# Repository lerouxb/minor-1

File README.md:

# minor-1

Credit card sized capacitive touch toy piano.

Just the absolute minimum:

* QT60140 16 key touch sensor
* ATtiny1614 microcontroller
* Piezo transducer
* MCP6001R op-amp as buffer for the piezo
* CR2032 coin cell battery
* SPDT power switch
* 13 keys, octave +/- and change sound touch buttons
* Currently unpopulated footprint for NOR flash
* P-channel MOSFET for completely cutting power

This uses the attiny's 8-bit DAC at 25khz to play notes. The microcontroller can shut down power to the op-amp/piezo and the flash chip when not in use. It also sleeps until a touch button is pressed or until there's activity on the serial port.

There's a simple browser page to log the button presses, read status and read/write the setups. Useful for configurating the touch controller. Could be useful in future for programming the NOR flash or configuring the sounds.

Still very much a work in progress, but it can already play tunes.

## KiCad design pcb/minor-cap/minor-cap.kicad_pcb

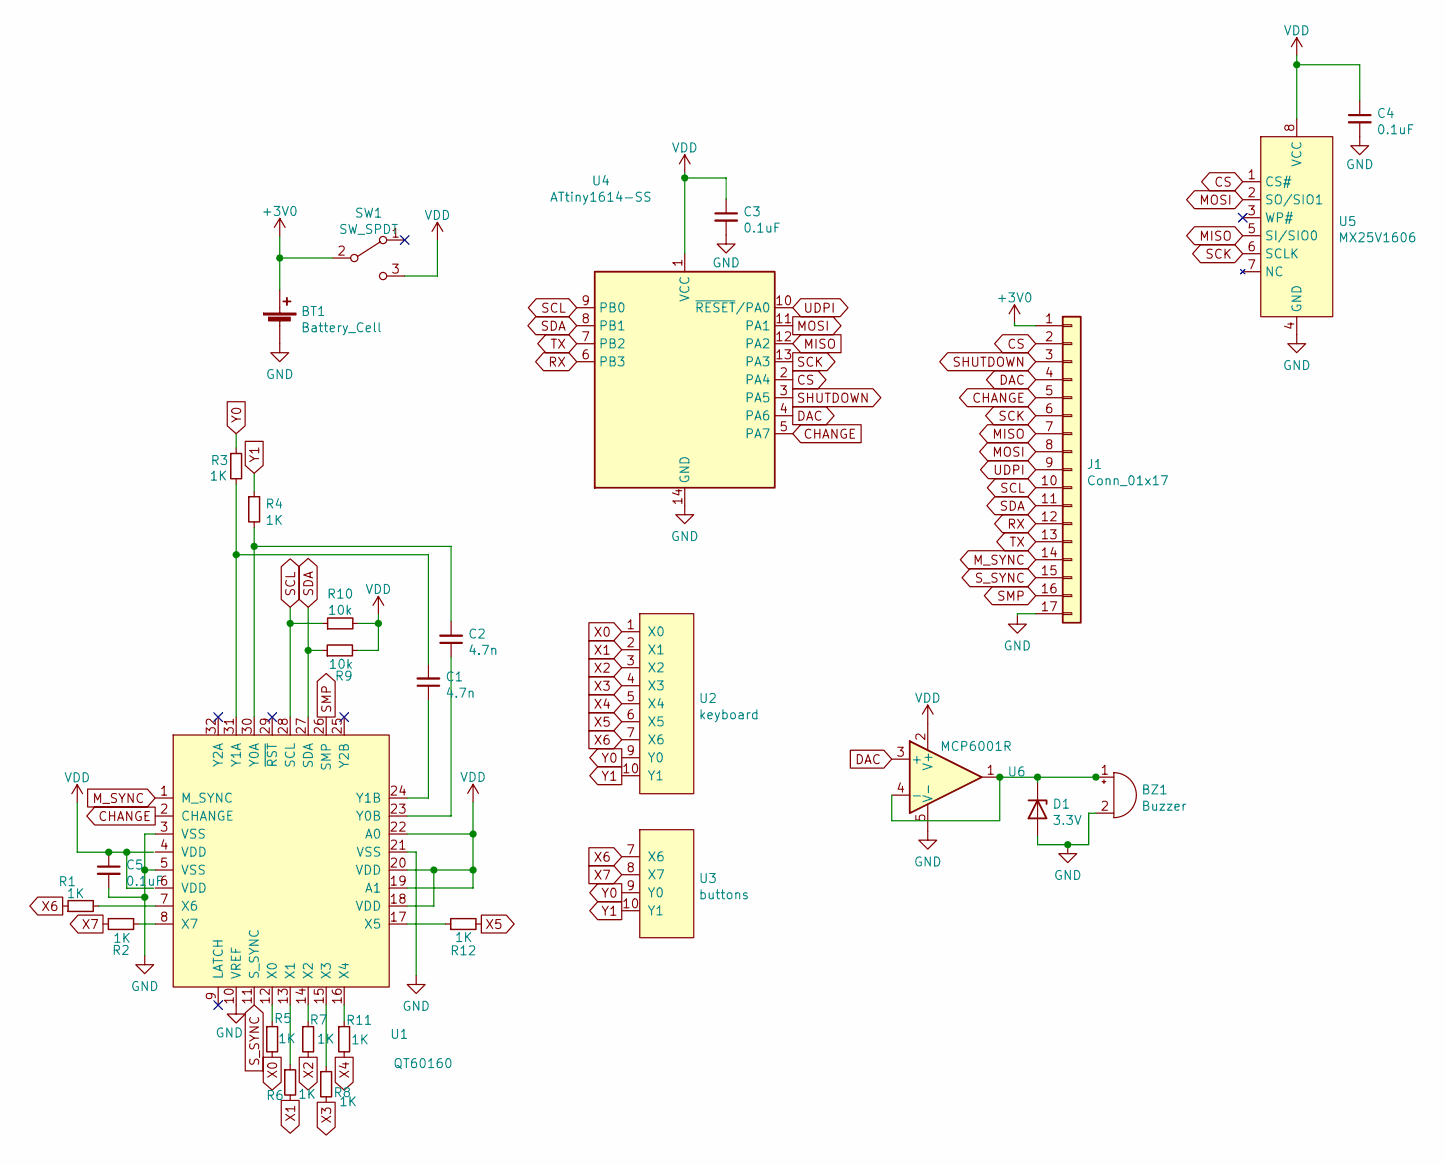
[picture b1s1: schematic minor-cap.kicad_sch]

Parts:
BT1: Battery_Cell; BatteryHolder_Keystone_3034_1x20mm
BZ1: Buzzer; Buzzer_Murata_PKLCS1212E
C1, C2: 4.7n; C_0603_1608Metric
C3, C4, C5: 0.1uF; C_0603_1608Metric
D1: 3.3V; D_SOD-323
J1: Conn_01x17; 01x17_custom
R1, R2, R3, R4, R5, R6, R7, R8, R11, R12: 1K; R_0603_1608Metric
R9, R10: 10k; R_0603_1608Metric
SW1: SW_SPDT; SW_SPDT_CK-JS102011SAQN
U1: QT60160; QFN-32-1EP_5x5mm_P0.5mm_EP3.1x3.1mm
U2: keyboard; 13-keys
U3: buttons; 3-buttons
U4: ATtiny1614-SS; SOIC-14_3.9x8.7mm_P1.27mm
U5: MX25V1606; SOP-8_3.9x4.9mm_P1.27mm
U6: MCP6001R; SOT-23-5

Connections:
+3V0: BT1.1 (+), J1.1, SW1.2 (B)
CHANGE: J1.5, U1.2 (CHANGE), U4.5 (PA7)
CS: J1.2, U4.2 (PA4), U5.1 (CS#)
DAC: J1.4, U4.4 (PA6), U6.3 (+)
GND: BT1.2 (-), BZ1.2 (+), C3.2, C4.2, C5.2, D1.2 (A), J1.17, U1.3 (VSS), U1.5 (VSS), U1.10 (VREF), U1.21 (VSS), U4.14 (GND), U5.4 (GND), U6.5 (V-)
MISO: J1.7, U4.12 (PA2), U5.5 (SI/SIO0)
MOSI: J1.8, U4.11 (PA1), U5.2 (SO/SIO1)
M_SYNC: J1.14, U1.1 (M_SYNC)
unnamed: BZ1.1 (-), D1.1 (K), U6.1, U6.4 (-)
unnamed: C1.1, U1.24 (Y1B)
unnamed: C1.2, R3.2, U1.31 (Y1A)
unnamed: C2.1, U1.23 (Y0B)
unnamed: C2.2, R4.2, U1.30 (Y0A)
unnamed: R1.2, U1.7 (X6)
unnamed: R2.1, U1.8 (X7)
unnamed: R5.1, U1.12 (X0)
unnamed: R6.1, U1.13 (X1)
unnamed: R7.1, U1.14 (X2)
unnamed: R8.1, U1.15 (X3)
unnamed: R11.1, U1.16 (X4)
unnamed: R12.1, U1.17 (X5)
RX: J1.12, U4.6 (PB3)
SCK: J1.6, U4.13 (PA3), U5.6 (SCLK)
SCL: J1.10, R10.1, U1.28 (SCL), U4.9 (PB0)
SDA: J1.11, R9.1, U1.27 (SDA), U4.8 (PB1)
SHUTDOWN: J1.3, U4.3 (PA5)
SMP: J1.16, U1.26 (SMP)
S_SYNC: J1.15, U1.11 (S_SYNC)
TX: J1.13, U4.7 (PB2)
UDPI: J1.9, U4.10 (~RESET~/PA0)
VDD: C3.1, C4.1, C5.1, R9.2, R10.2, SW1.3 (C), U1.18 (VDD), U1.19 (A1), U1.20 (VDD), U1.22 (A0), U4.1 (VCC), U5.8 (VCC), U6.2 (V+)
X0: R5.2, U2.1 (X0)
X1: R6.2, U2.2 (X1)
X2: R7.2, U2.3 (X2)
X3: R8.2, U2.4 (X3)
X4: R11.2, U2.5 (X4)
X5: R12.2, U2.6 (X5)
X6: R1.1, U2.7 (X6), U3.7 (X6)
X7: R2.2, U3.8 (X7)
Y0: R3.1, U2.9 (Y0), U3.9 (Y0)
Y1: R4.1, U2.10 (Y1), U3.10 (Y1)

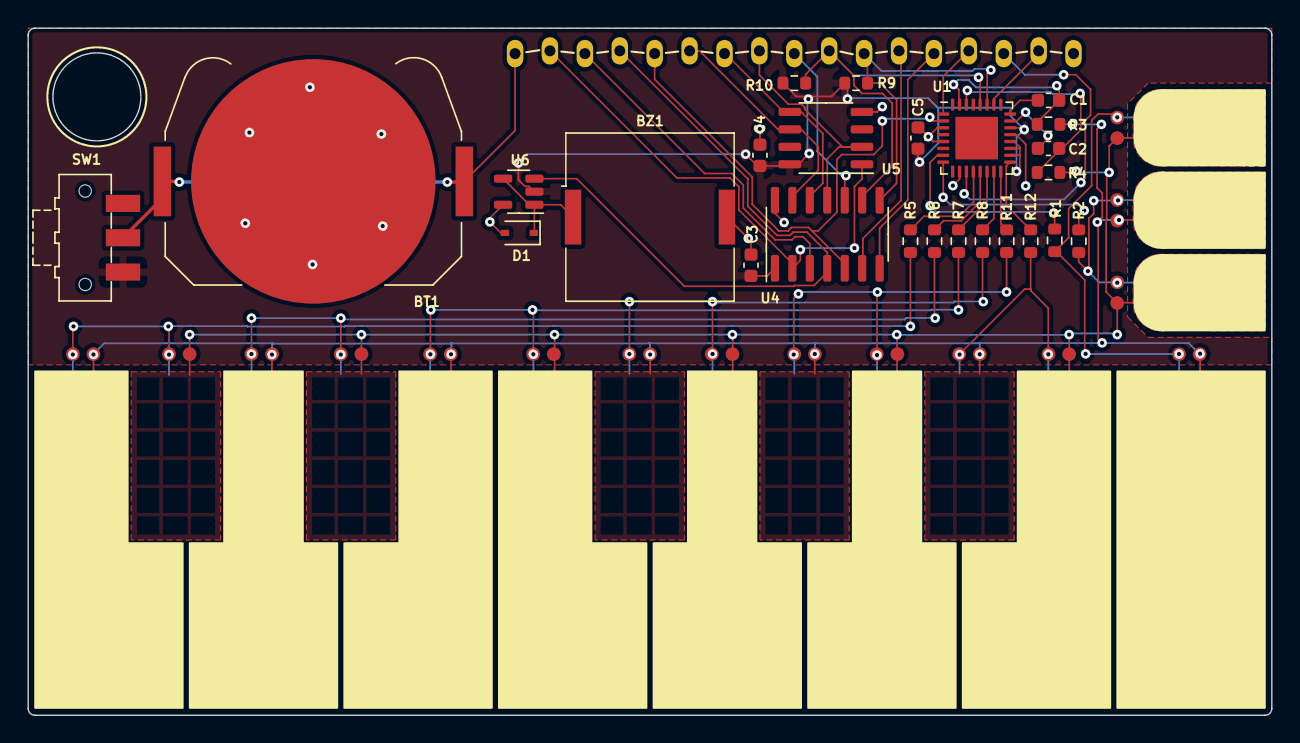
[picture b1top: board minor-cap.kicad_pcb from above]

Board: 2 copper layers, 90.5 x 50.0 mm, 28 parts (0 on the bottom side), 41 nets.

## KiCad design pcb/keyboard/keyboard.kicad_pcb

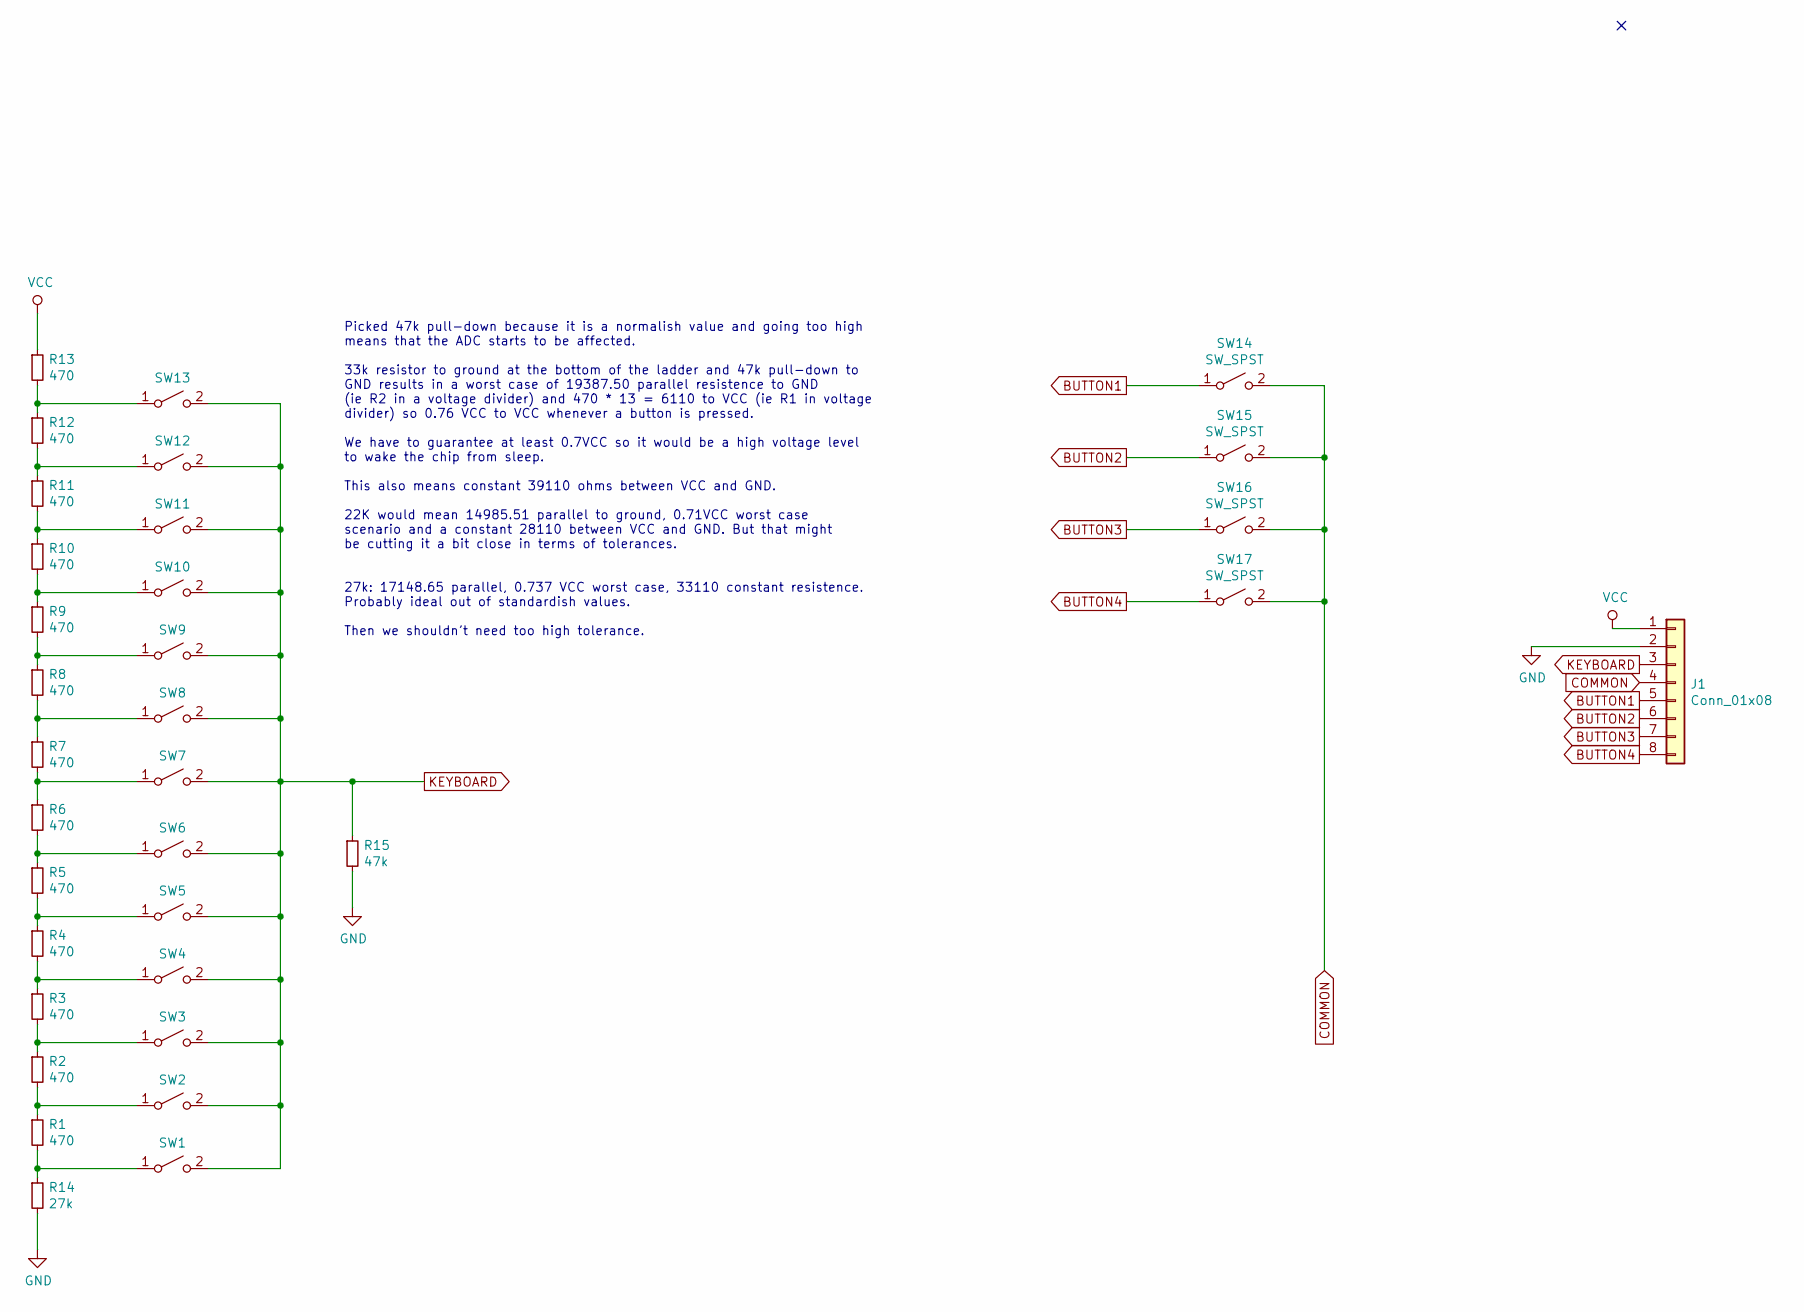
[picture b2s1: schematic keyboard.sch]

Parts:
J1: Conn_01x08; Pin_Header_Straight_1x08_Pitch2.54mm
R1, R2, R3, R4, R5, R6, R7, R8, R9, R10, R11, R12, R13: 470; R_0603
R14: 27k; R_0603
R15: 47k; R_0603
SW1, SW2, SW3, SW4, SW5, SW6, SW7, SW8, SW9, SW10, SW11, SW12, SW13, SW14, SW15, SW16, SW17: SW_SPST; EVQ-Q2B03W

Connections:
BUTTON1: J1.5, SW14.1 (A)
BUTTON2: J1.6, SW15.1 (A)
BUTTON3: J1.7, SW16.1 (A)
BUTTON4: J1.8, SW17.1 (A)
COMMON: J1.4, SW14.2 (B), SW15.2 (B), SW16.2 (B), SW17.2 (B)
GND: J1.2, R14.2, R15.2
KEYBOARD: J1.3, R15.1, SW1.2 (B), SW2.2 (B), SW3.2 (B), SW4.2 (B), SW5.2 (B), SW6.2 (B), SW7.2 (B), SW8.2 (B), SW9.2 (B), SW10.2 (B), SW11.2 (B), SW12.2 (B), SW13.2 (B)
unnamed: R1.1, R2.2, SW2.1 (A)
unnamed: R1.2, R14.1, SW1.1 (A)
unnamed: R2.1, R3.2, SW3.1 (A)
unnamed: R3.1, R4.2, SW4.1 (A)
unnamed: R4.1, R5.2, SW5.1 (A)
unnamed: R5.1, R6.2, SW6.1 (A)
unnamed: R6.1, R7.2, SW7.1 (A)
unnamed: R7.1, R8.2, SW8.1 (A)
unnamed: R8.1, R9.2, SW9.1 (A)
unnamed: R10.1, R11.2, SW11.1 (A)
unnamed: R9.1, R10.2, SW10.1 (A)
unnamed: R11.1, R12.2, SW12.1 (A)
unnamed: R12.1, R13.2, SW13.1 (A)
VCC: J1.1, R13.1

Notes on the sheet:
Picked 47k pull-down because it is a normalish value and going too high means that the ADC starts to be affected. 33k resistor to ground at the bottom of the ladder and 47k pull-down to GND results in a worst case of 19387.50 parallel resistence to GND (ie R2 in a voltage divider) and 470 * 13 = 61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

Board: 2 copper layers, 33 parts (0 on the bottom side), 21 nets, no tracks yet.

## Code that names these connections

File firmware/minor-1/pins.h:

#ifndef PINS_H
#define PINS_H

#include <arduino.h>

//#define LED_PIN (PIN_PB4)
#define SHUTDOWN_PIN (PIN_PA5)
#define DAC_PIN (PIN_PA6)
#define CHANGE_PIN (PIN_PA7)

#endif

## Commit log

2021-02-21 initial test code
2021-02-21 inlining
2021-02-21 add TIMER_0
2021-02-27 attiny3216
2021-02-27 ignore some stuff
2021-02-28 notes
2021-02-28 10mhz
2021-02-28 0.55V DAC Ref
2021-03-02 pcb mockup
2021-03-02 32bits
2021-03-02 LED, button debounce
2021-03-02 remove unused file
2021-03-03 octave switching
2021-03-03 cleanup
2021-03-04 saw and triangle
2021-03-14 back to arduino
2021-04-18 before silkscreen
2021-04-19 routed
2021-04-20 ignore backups
2021-07-14 firmware
2021-07-14 README
